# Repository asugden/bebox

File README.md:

#BEBOX

BeBox is a collection of tools for systems neuroscience. It includes three parts: designs for 3d printing, circuits and printed circuit boards (PCBs) for behavioral manipulation, and the Arduino code necessary for those circuits.

Many people are interested in only the 3d designs. In that case, all necessary hardware components are listed in the 3d designs directory. If you are interested in electronics, the BeBox Spritz and the BeBox Syringe Pump can both be used indepent of the BeBox system. The syringe pump can be integrated with BeBox. To start with BeBox, one has to order the boards (links can be found in the pcb directory), which come in orders of 3 from OSH Park, my preferred supplier. Note that BeBox is connected by 4-conductor headphone cables. They can be a bit hard to find. 3-conductor cables will not work.

##3D DESIGNS:
__All necessary components are listed in the README in the 3d directory.__

- .stl files  are final output files to be used with 3D printers.
- .scad files  are files written in OpenSCAD which define the .stl files and can be edited
- Some designs are made in Fusion 360 and are available upon request.

###bebox
- bebox bnc bottom.stl  the bottom of a case to hold bnc connectors for bebox
- bebox bnc top.stl  the top of the case to hold bnc connectors for bebox, which can have magnets inserted to allow stacking
- bebox button bottom.stl  the bottom of a case to hold bebox buttons, which also reports licks
- bebox button top.stl  the top of the case to hold bebox buttons
- bebox button 1.stl  a button cap with the number 1
- bebox button 2.stl  a button cap with the number 2
- bebox button 3.stl  a button cap with the number 3
- bebox button 4.stl  a button cap with the number 4
- bebox button e.stl  a button cap with the number e, for ensure
- bebox button q.stl  a button cap with the letter q, for quinine
- bebox main bottom.stl  the bottom of the case to hold the main bebox board
- bebox main top.stl  the top of the case to hold the main bebox board

###lickspout
__NOTE:__ the lickspouts should be printed with conductive PLA if conductive measurement is desired. The lickspout base should be printed in regular PLA. Conductive PLA plastic can be found at https://www.proto-pasta.com/collections/exotic-composite-pla/products/conductive-pla

- lickspout bitube.stl  a pre-made file to be printed with conductive filament that has two tubes, one regularly used for ensure high-calorie milkshake and one used for quinine diluted in water. This is designed for Tygon tubing of 1/16 inch inner diameter and 1/8 inch outer diameter (1.6 mm ID/3.2 mm OD). 
- lickspout unitube.stl  a pre-made file to be printed with conductive filament that has a single tube with a collection area, for training on only a high-calorie milkshake
- lickspout.scad  the file used to create both lickspout bitube and lickspout unitube. Adjustments can be made to the tube diameters at the top. Note that the curved pipe library is required for making changes: https://www.thingiverse.com/thing:71464
- lickspout bitube water.stl  a pre-made file to be printed with conductive filament that has two narrow-diameter tubes. The input tubing should be the same diameter, but the flow rate is decreased
- lickspout water.scad  the file used to create lickspout bitube water.stl. This, too, depends on the curved pipe library
- utilities.scad  a set of useful functions for OpenSCAD

###syringe-pump
The syringe pump is designed to tightly fit 20 ml syringes. All necessary mechanical and electrical components are listed in the README of the syringe 

- syringe pump box.stl  a file that defines the enclosure of the syringe pump including the motor and carriage
- syringe pump carriage.stl  the carriage that rides along bearings to compress the syringe. Note that it should be printed vertically rather than on a flat face.

###wheel
- wheel.stl  a pre-made file that can be printed on an average FDM printer with minimal layer heights. This requires two M4 nuts to be embedded and two M4x10 bolts to pinch the axles. I recommend using black PLA for the wheel as other colors may not correctly block the IR light of a beam breaker. We had problems with gray PLA being transparent to IR light.
- wheel axle.stl  a pre-made file of a short axle piece used to attach the wheel to the wheel holder. 2 are required
- wheel holder.stl  a pre-made file of a suspension system for the wheel, designed to fit into standard Thorlabs pieces. Requires two bearings from McMaster-Carr catalog number 57155K323 at $5.70 each to be inserted into the large central holes with the flanges outward. We hot glue them in, taking care not to get the glue into the bearings.
- wheel.scad  the file used to create wheel.stl. The wheel height, diameter, and tab spacing can all be changed. Note that a finer tab spacing requires narrower LED beam break detectors-- do not change without changing the encoder board.
- wheel holder.scad  the file used to create wheel axle.stl. The spring width, length, and thickness can all be adjusted and the wheel position will remain constant.

###wheel-accessories
- wheel run stopper.stl  a pre-made file that fits into a thorlabs part and applies some resistance to the wheel without disrupting its low inertia/springiness
- wheel run stopper.scad  the file used to create wheel run stopper.stl

###wheel-encoder
__NOTE:__ will be udpated in the near future

- wheel arduino holder.stl  a file to hold two LED beam breakers adjacent to the wheel
- wheel encoder board holder.stl  a file to allow an arduino to be bolted on to the holder such that it can be held next to the wheel

##ARDUINO CODE:
__NOTE:__ Has not yet been made compatible with the new BeBox system. Will be updated soon.

- BeBox  the code to run the BeBox system
	- mpr121.h  the header definitions required for the capacitance lick detection system

- Dumberbox  the code used to run the legacy Dumbberbox
- Encoder_Scanbox  the code used to run the legacy scanbox rotary encoder. Will be replaced with BeBox encoder software in early April 2019.

##PCB DESIGNS:
__All necessary components are listed in the README in the pcb directory.__

- .brd files  board files, matched with their schematic file, made in Eagle. You can bypass dealing with these files by directly ordering from OSH Park through a link I've set up. I am not affiliated with OSH Park.
- .sch files  schematic files, matched with a board file, made in Eagle. 

__NOTE:__  PCBs can be ordered from OSH Park for low costs. As of now, they are untested so please wait until late March 2019

- bebox_main  the main board, which takes power and connects directly to high-current behavior systems such as solenoids. It passed on the power given to it (usually 12V 2A supply, but can be 6-13 V and > 1 A). It connects via headphone cables to the daughter boards and lick spout. The connection ports are interchangeable.
- bebox_bnc  a daughterboard that allows for connections with Matlab via a Nidaq BNC system. It includes the lick detection and 4 output solenoids
- bebox_buttons  a daughterboard that allows control of solenoids and reports licking. There are two lick detection LEDs, just in case, and four buttons to control solenoids.
- bebox_encoder  a board that holds the rotary encoder IR beam breakers adjacent to the running wheel. This board can be configured in one of three ways: 
	1. For connection to the BeBox system, one can solder on an Adafruit Metro Mini (an Arduino Uno clone that has been miniaturized) and the i2c headphone jack. This will allow BeBox to directly interact with the running encoder. 
	2. To connect to Neurolabware's Scanbox, one can solder on an Adafruit Metro Mini and no headphone jacks. This can be plugged directly into the Scanbox computer via USB and it will be indistinguishable from an Arduino Uno.
	3. To use this with systems sensitive to electrical noise (electrophysiology), one can solder on the "ephys only" headphone jack, which transmits ground, power, and the output of the two beam breakers. This i2c cable can pass outside of a faraday cage to an external Arduino.

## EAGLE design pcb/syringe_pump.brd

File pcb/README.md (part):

__NOTE: I get no money from this and have no affiliation with OSH Park.__

## BeBox Main Trinket components

__CONFIRMED TO WORK__: https://oshpark.com/shared_projects/5AUOipvb

After creating this PCB, the Trinket became deprecated. I have created a newer, faster version based on the Adafruit ItsyBitsy M4.

| Part name            | Count | Cost per part | Total cost | Vendor  | Vendor part number | 
|----------------------|-------|---------------|------------|---------|--------------------| 
| headone jack         | 4     | 1.66          | 6.64       | Digikey | CP-435107RS-ND     | 
| 4.7k resistor        | 6     | 0.10          | 0.60       | Digikey | CF14JT4K70CT-ND    | 
| power jack           | 1     | 0.76          | 0.76       | Digikey | CP-102AH-ND        | 
| screw terminal       | 4     | 0.75          | 3.00       | Digikey | ED2740-ND          | 
| switch               | 1     | 11.56         | 11.56      | Digikey | 679-3961-ND        | 
| diode                | 4     | 0.11          | 0.44       | Digikey | 641-1310-1-ND      | 
| transistor           | 4     | 0.70          | 2.80       | Digikey | TIP122GOS-ND       | 
| adafruit pro trinket | 1     | 9.95          | 9.95       | Digikey | 1528-1039-ND       | 

## BeBox Main ItsyBitsy components

https://oshpark.com/shared_projects/iDtDUlNY

This new version is based on the Adafruit ItsyBitsy M4, but requires conversion for logic levels.

| Part name              | Count | Cost per part | Total cost | Vendor  | Vendor part number | 
|------------------------|-------|---------------|------------|---------|--------------------| 
| headone jack           | 4     | 1.66          | 6.64       | Digikey | CP-435107RS-ND     | 
| 4.7k resistor          | 8     | 0.10          | 0.60       | Digikey | CF14JT4K70CT-ND    | 
| power jack             | 1     | 0.76          | 0.76       | Digikey | CP-102AH-ND        | 
| screw terminal         | 4     | 0.75          | 3.00       | Digikey | ED2740-ND          | 
| switch                 | 1     | 11.56         | 11.56      | Digikey | 679-3961-ND        | 
| diode                  | 4     | 0.11          | 0.44       | Digikey | 641-1310-1-ND      | 
| transistor             | 4     | 0.70          | 2.80       | Digikey | TIP122GOS-ND       | 
| adafruit itsybitsy m4  | 1     | 9.95          | 9.95       | Digikey | 1528-1039-ND       | 
| logic level transistor | 2     | 0.47          | 0.94       | Digikey | 2N7000FS-ND        | 
| 5V regulator           | 1     | 6.81          | 20.43      | Digikey | 945-1037-ND        | 

## BeBox BNC components

__CONFIRMED TO WORK__: https://oshpark.com/shared_projects/NPiqw07m

This box breaks out BNCs for communication with NIDAQ boards or the like. Currently, there is only a single lick output. Although the rest of BeBox can handle two capacitive sensors, the BNC board is not yet adapted for 4 solenoids and 2 licks. It is easy to change the code such that one of the solenoid inputs can be converted to a second lick output.

| Part name       | Count | Cost per part | Total cost | Vendor  | Vendor part number | 
|-----------------|-------|---------------|------------|---------|--------------------| 
| bnc onnector    | 5     | 1.65          | 8.25       | Digikey | A97555-ND          | 
| headphone jack  | 1     | 1.66          | 1.66       | Digikey | CP-435107RS-ND     | 
| i2c io expander | 1     | 1.05          | 1.05       | Digikey | MCP23008-E/P-ND    | 
| 4.7k resistor   | 5     | 0.10          | 0.50       | Digikey | CF14JT4K70CT-ND    | 

## BeBox Button components

__CONFIRMED TO WORK__: https://oshpark.com/shared_projects/y1Swevmm

This box has buttons to control solenoids, as well as two LEDs that represent responses to different capacitance inputs. Our printer and slicer do a poor job keeping the inside of the LED holes clean, so it sometimes needs to be cleaned out with a 5 mm / 3/16 inch drill bit.

| Part name       | Count | Cost per part | Total cost | Vendor  | Vendor part number | 
|-----------------|-------|---------------|------------|---------|--------------------| 
| headphone jack  | 1     | 1.66          | 1.66       | Digikey | CP-435107RS-ND     | 
| i2c io expander | 1     | 1.05          | 1.05       | Digikey | MCP23008-E/P-ND    | 
| switch (cherry) | 4     | 0.90          | 3.60       | Digikey | CH310-ND           | 
| 330 resistor    | 2     | 0.10          | 0.20       | Digikey | CF14JT330RCT-ND    | 
| red led         | 1     | 0.33          | 0.33       | Digikey | 160-1853-ND        | 
| yellow led      | 1     | 0.33          | 0.33       | Digikey | 160-1851-ND        | 

## BeBox cables

You need 4-conductor 3.5 mm headphone cables to connect BeBox components. They can be any length. Two cables are required for the main 3 boxes, but more need to be used for the encoder or syringe pump. Below are options– you can choose how many to order of each size.

| Part name  | Count | Cost per part | Total cost | Vendor    | Vendor part number | 
|------------|-------|---------------|------------|-----------|--------------------| 
| 1' cable   | 1     | 1.50          | 1.50       | Digikey   | CAB-14163-ND       | 
| 3' cable   | 1     | 2.50          | 2.50       | Digikey   | CAB-14164-ND       | 
| 6' cable   | 1     | 6.45          | 6.45       | Digikey   | CP-354S-M/M-ND     | 
| 1' cable   | 1     | 1.89          | 1.89       | Monoprice | 24437              | 
| 3' cable   | 1     | 2.29          | 2.29       | Monoprice | 18632              | 
| 6' cable   | 1     | 2.59          | 2.59       | Monoprice | 18633              | 

## BeBox Capacitance Lickspout components

__CONFIRMED TO WORK__

There is no PCB here. We simply order a capacitance-sensing board and wire in the 4-conductor headphone cable. One prints a capacitance lickspout, uses an M3 bolt to fasten it to the lickspout holder, solder headers into the capacitance sensing board, heat a wire and shove it into the lickspout, and then attach it to the capacitance sensing board (again with headers, so that the lickspout can be replaced often).

__CONNECT BLACK -> SCL, YELLOW -> SDA, GREEN -> GND, RED -> VIN__

Note that wires are connected differently from dumberboxes.

| Part name          | Count | Cost per part | Total cost | Vendor  | Vendor part number | 
|--------------------|-------|---------------|------------|---------|--------------------| 
| capacitance sensor | 1     | 7.95          | 7.95       | Digikey | CP-435107RS-ND     | 
| 4-conductor wire   | 1     | 6.25          | 6.25       | Digikey | CP-354S-ND         | 
| female header      | 1     | 0.32          | 0.32       | Digikey | S7000-ND           | 

## BeBox Encoder components

https://oshpark.com/shared_projects/I9CImQTS

| Part name           | Count | Cost per part | Total cost | Vendor  | Vendor part number | 
|---------------------|-------|---------------|------------|---------|--------------------| 
| ir beam break       | 2     | 3.77          | 7.54       | Digikey | 1855-1043-ND       | 
| 220 resistor        | 2     | 0.10          | 0.20       | Digikey | CF14JT220RCT-ND    | 
|                     |       |               |            |         |                    | 
| OPTIONAL:           |       |               |            |         |                    | 
| adafruit metro mini | 1     | 12.50         | 12.50      | Digikey | 1528-1374-ND       | 
| headphone jack      | 1     | 1.66          | 1.66       | Digikey | CP-435107RS-ND     | 

This board can be configured in one of three ways: 

1. For connection to the BeBox system, one can solder on an Adafruit Metro Mini (an Arduino Uno clone that has been miniaturized) and the i2c headphone jack. This will allow BeBox to directly interact with the running encoder.  __(both optional components)__
2. To connect to Neurolabware's Scanbox, one can solder on an Adafruit Metro Mini and no headphone jacks. This can be plugged directly into the Scanbox computer via USB and it will be indistinguishable from an Arduino Uno.  __(only optional metro mini)__
3. To use this with systems sensitive to electrical noise (electrophysiology), one can solder on the "ephys only" headphone jack, which transmits ground, power, and the output of the two beam breakers. This i2c cable can pass outside of a faraday cage to an external Arduino.  __(only optional headphone jack)__

## BeBox Syringe Pump components

https://oshpark.com/shared_projects/pRGppHBK

The syringe pump also requires a replaceable 20 ml syringe.

| Part name                                 | Count | Cost per part | Total cost | Vendor  | Vendor part number    | 
|-------------------------------------------|-------|---------------|------------|---------|-----------------------| 
| adafruit itsybitsy m4                     | 1     | 14.95         | 14.95      | Digikey | 1528-2619-ND          | 
| stepper driver                            | 1     | 7.98          | 23.94      | Digikey | 1460-1159-ND          | 
| 5V regulator                              | 1     | 6.81          | 20.43      | Digikey | 945-1037-ND           | 
| oled screen                               | 1     | 19.95         | 19.95      | Digikey | 1528-1512-ND          | 
| switch (cherry MX clear)                  | 1     | 0.90          | 0.90       | Digikey | CH310-ND              | 
| rotary encoder (long)                     | 1     | 1.73          | 1.73       | Digikey | PEC11R-4020F-S0012-ND | 
| forward-backward toggle switch            | 1     | 4.32          | 4.32       | Digikey | 360-3355-ND           | 
| on-off toggle switch                      | 1     | 5.96          | 5.96       | Digikey | M2012S2A2A30-ND       | 
| power jack                                | 1     | 0.76          | 0.76       | Digikey | CP-102AH-ND           | 
| screw terminal                            | 4     | 0.75          | 3.00       | Digikey | ED2740-ND             | 
| heat sink pad                             | 1     | 3.44          | 3.44       | Digikey | 3M10304-ND            | 
| heatsink                                  | 1     | 0.49          | 1.47       | Digikey | AE11388-ND            | 
| logic level transistor                    | 2     | 0.47          | 0.94       | Digikey | 2N7000FS-ND           | 
| 4.7k resistor                             | 4     | 0.10          | 0.40       | Digikey | CF14JT4K70CT-ND       | 
| 3.5mm jack                                | 1     | 1.66          | 1.66       | Digikey | CP-435107RS-ND        | 
| stepper motor (NEMA 17 200 steps/rev 12V) | 1     | 14.00         | 14.00      | Digikey | 1528-1062-ND          | 

## BeBox Spritz components

https://oshpark.com/shared_projects/YoxiTIt1

This is a device to produce very small amounts of pressure for microinjections or puffing of drugs onto slices.

| Part name                | Count | Cost per part | Total cost | Vendor   | Vendor part number    | 
|--------------------------|-------|---------------|------------|----------|-----------------------| 
| adafruit itsybitsy m4    | 1     | 14.95         | 14.95      | Digikey  | 1528-2619-ND          | 
| 5V regulator             | 1     | 6.81          | 20.43      | Digikey  | 945-1037-ND           | 
| oled screen              | 1     | 19.95         | 19.95      | Digikey  | 1528-1512-ND          | 
| switch (cherry MX clear) | 2     | 0.90          | 1.80       | Digikey  | CH310-ND              | 
| rotary encoder (long)    | 1     | 1.73          | 1.73       | Digikey  | PEC11R-4020F-S0012-ND | 
| on-off toggle switch     | 1     | 5.96          | 5.96       | Digikey  | M2012S2A2A30-ND       | 
| power jack               | 1     | 0.76          | 0.76       | Digikey  | CP-102AH-ND           | 
| 150 resistor             | 1     | 0.10          | 0.10       | Digikey  | CF14JT150RCT-ND       | 
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
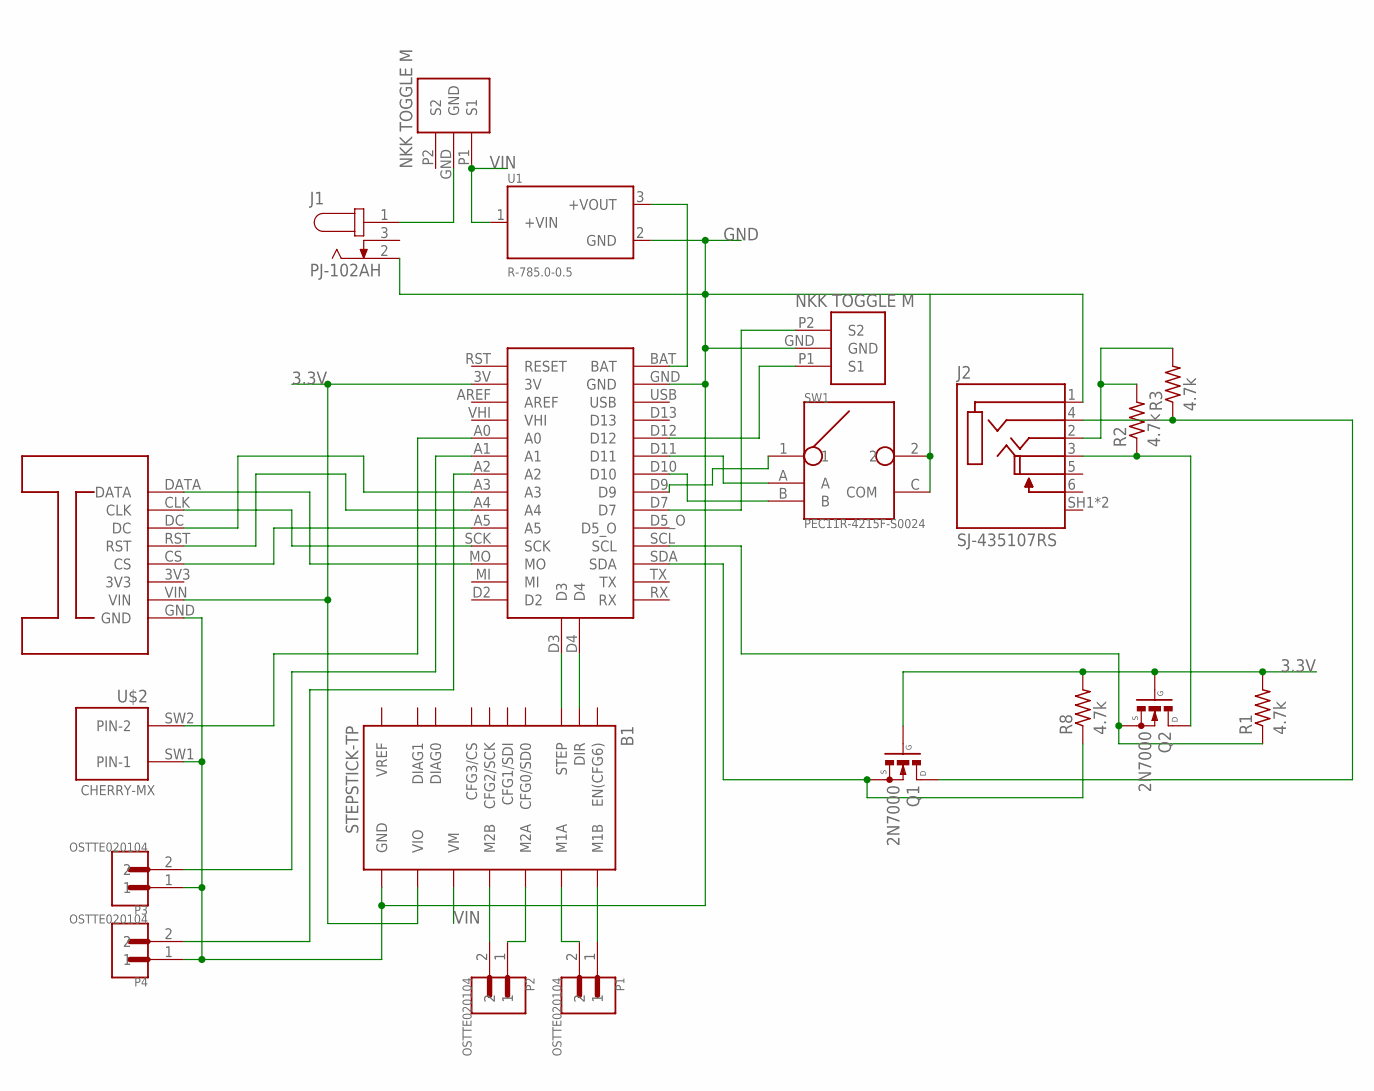
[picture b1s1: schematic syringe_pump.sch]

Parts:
B1: STEPSTICK-TP; STEPSTICK_TP
J1: PJ-102AH; CUI_PJ-102AH
J2: SJ-435107RS; CUI_SJ-435107RS
P1, P2, P3, P4: OSTTE020104; OST_OSTTE020104
Q1, Q2: 2N7000; TO92
R1, R2, R3, R8: 4.7k; 0207/10
SW1: PEC11R-4215F-S0024; SW_PEC11R-4215F-S0024
U1: R-785.0-0.5; RECOM_R-785.0-0.5
U$1: ITSYBITSYM4
U$2: CHERRY-MX
U$3: OLED_128X64
U$4: NKK_M2012S2A2A30
U$5: NKK_B13AH

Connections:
3.3V: B1.VIO, Q1.2 (G), Q2.2 (G), R1.2, R8.2, U$1.3V, U$3.VIN
GND: B1.GND@1 (GND), B1.GND@2 (GND), J1.2, J2.1 (SLEEVE), P3.1, P4.1, SW1.2, SW1.C (COM), U1.2 (GND), U$1.GND, U$2.SW1 (PIN-1), U$3.GND, U$5.GND
unnamed: Q1.1 (S), R8.1, U$1.SDA
unnamed: J2.2 (TIP), R2.2, R3.2
unnamed: B1.STEP, U$1.D3
unnamed: B1.DIR, U$1.D4
unnamed: Q2.1 (S), R1.1, U$1.SCL
unnamed: B1.M2B, P2.2
unnamed: B1.M2A, P2.1
unnamed: B1.M1B, P1.1
unnamed: B1.M1A, P1.2
unnamed: J2.3 (RING1), Q2.3 (D), R2.1
unnamed: J2.4 (RING2), Q1.3 (D), R3.1
unnamed: U$1.MO, U$3.DATA
unnamed: U$1.A3, U$3.DC
unnamed: U$1.A5, U$3.CS
unnamed: U$1.A4, U$3.RST
unnamed: P4.2, U$1.A2
unnamed: U$1.SCK, U$3.CLK
unnamed: J1.1, U$4.GND
unnamed: P3.2, U$1.A1
unnamed: U$1.A0, U$2.SW2 (PIN-2)
unnamed: U$1.D12, U$5.P1 (S1)
unnamed: U$1.D7, U$5.P2 (S2)
unnamed: SW1.A, U$1.D11
unnamed: SW1.B, U$1.D10
unnamed: SW1.1, U$1.D9
unnamed: U1.3 (+VOUT), U$1.BAT
VIN: B1.VM, U1.1 (+VIN), U$4.P1 (S1)

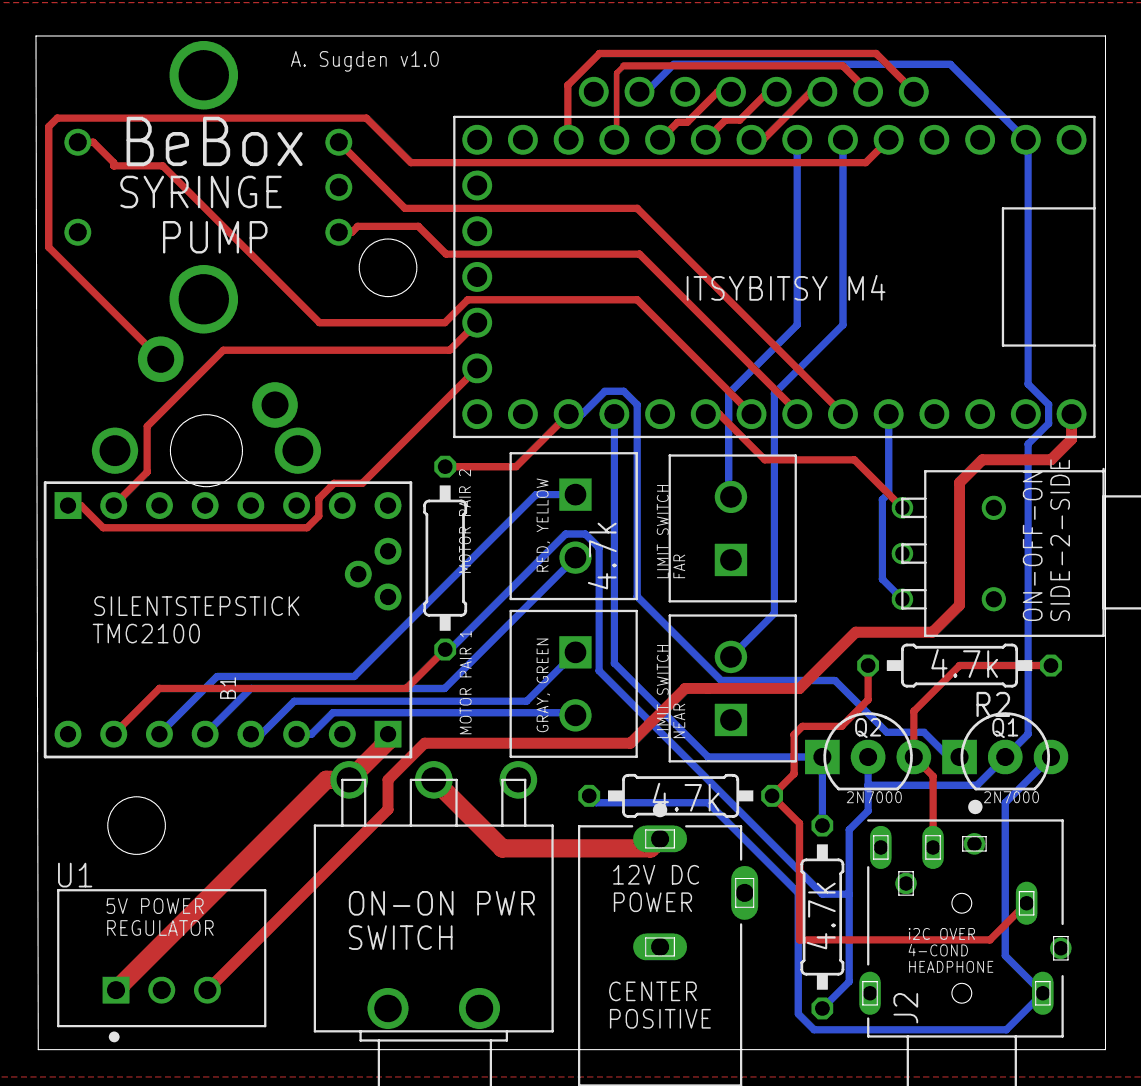
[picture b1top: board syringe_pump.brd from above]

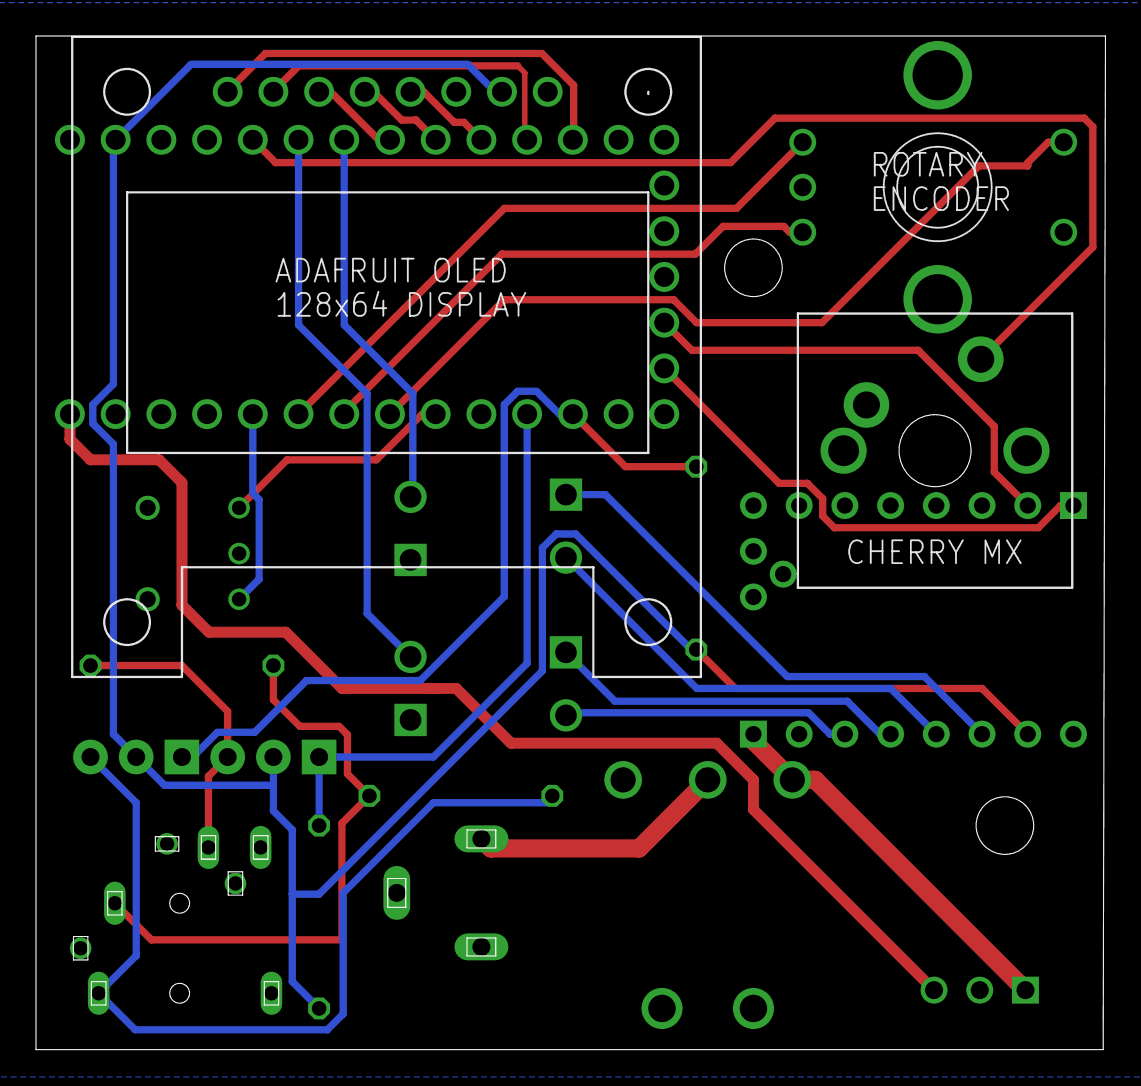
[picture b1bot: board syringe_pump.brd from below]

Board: 2 copper layers, 59.4 x 56.3 mm, 20 parts (3 on the bottom side), 29 nets.

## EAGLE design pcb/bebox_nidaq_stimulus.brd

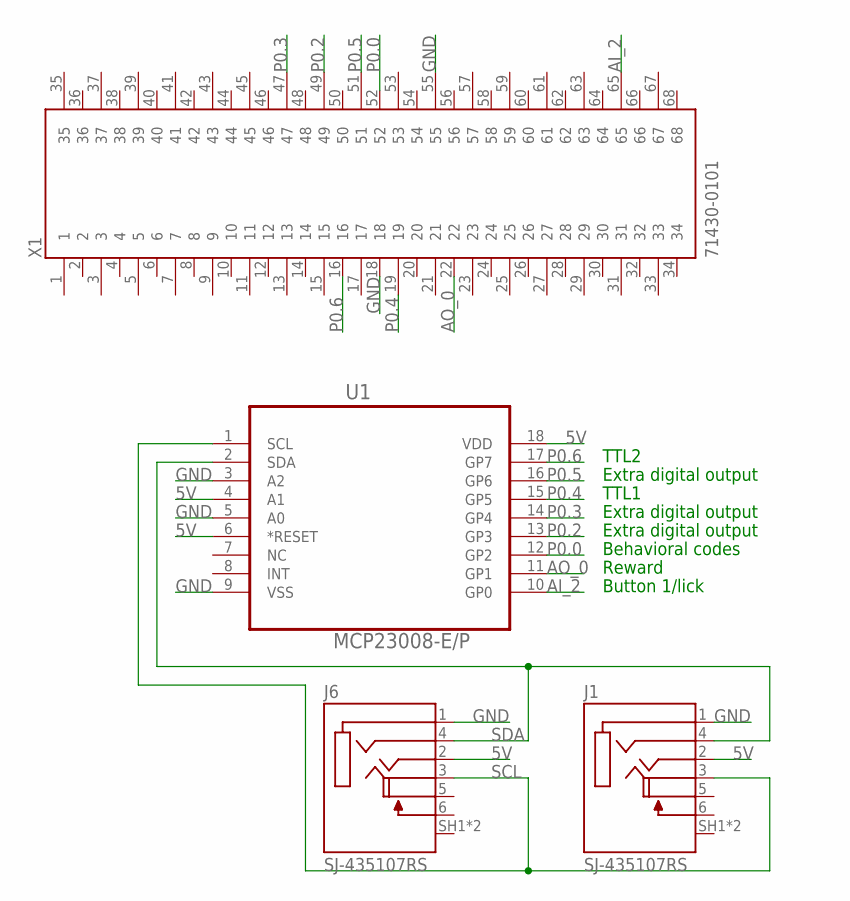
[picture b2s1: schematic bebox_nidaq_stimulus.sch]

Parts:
J1, J6: SJ-435107RS; CUI_SJ-435107RS
U1: MCP23008-E/P; DIP254P762X533-18
X1: 71430-0101; MOLEX_71430-0101

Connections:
5V: J1.2 (TIP), J6.2 (TIP), U1.4 (A1), U1.6 (*RESET), U1.18 (VDD)
AI_2: U1.10 (GP0), X1.65
AO_0: U1.11 (GP1), X1.22
GND: J1.1 (SLEEVE), J6.1 (SLEEVE), U1.3 (A2), U1.5 (A0), U1.9 (VSS), X1.18, X1.55
P0.0: U1.12 (GP2), X1.52
P0.2: U1.13 (GP3), X1.49
P0.3: U1.14 (GP4), X1.47
P0.4: U1.15 (GP5), X1.19
P0.5: U1.16 (GP6), X1.51
P0.6: U1.17 (GP7), X1.16
SCL: J1.3 (RING1), J6.3 (RING1), U1.1 (SCL)
SDA: J1.4 (RING2), J6.4 (RING2), U1.2 (SDA)

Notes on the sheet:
Reward
Behavioral codes
Button 1/lick
TTL1
TTL2
Extra digital output

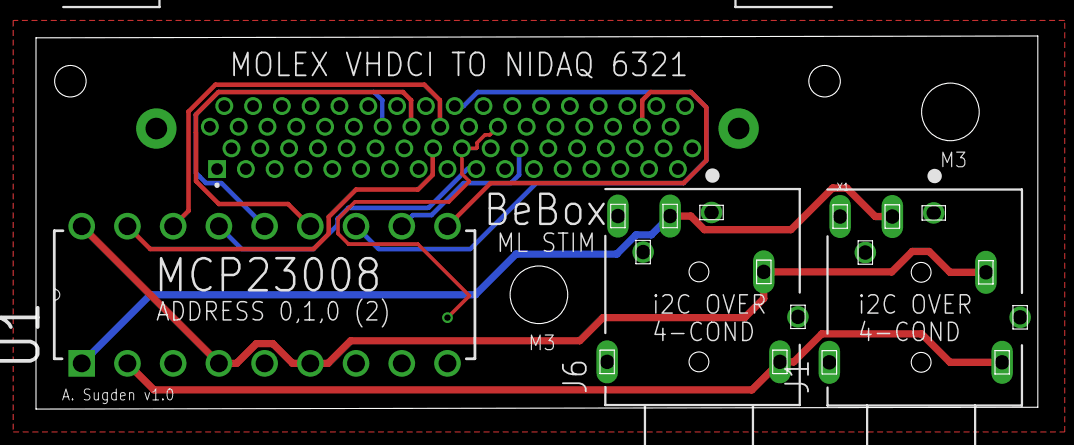
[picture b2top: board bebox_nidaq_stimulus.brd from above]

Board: 2 copper layers, 55.7 x 20.7 mm, 4 parts (0 on the bottom side), 12 nets.

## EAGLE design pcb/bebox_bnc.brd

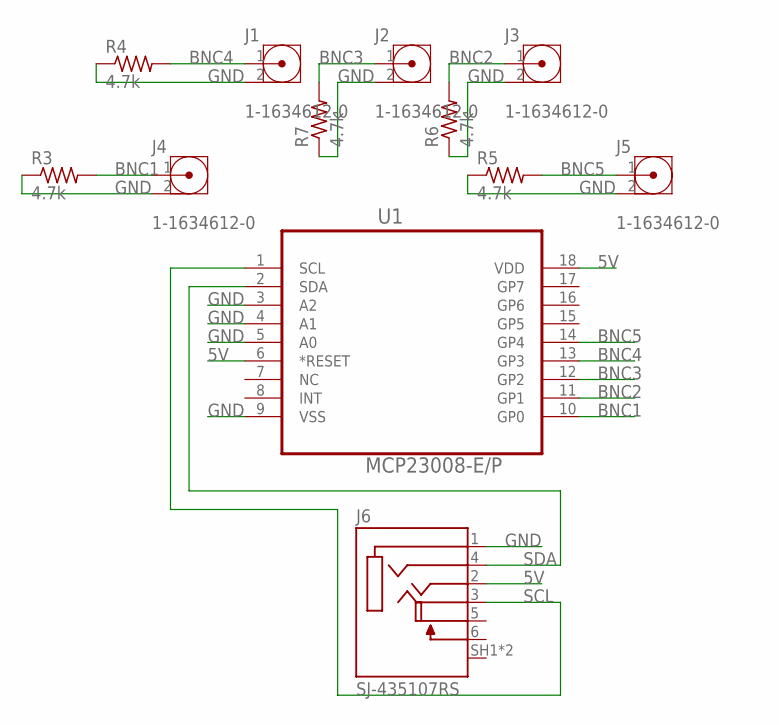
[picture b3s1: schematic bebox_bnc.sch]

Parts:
J1, J2, J3, J4, J5: 1-1634612-0; TE_1-1634612-0
J6: SJ-435107RS; CUI_SJ-435107RS
R3, R4, R5, R6, R7: 4.7k; 0207/10
U1: MCP23008-E/P; DIP254P762X533-18

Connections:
5V: J6.2 (TIP), U1.6 (*RESET), U1.18 (VDD)
BNC1: J4.1, R3.2, U1.10 (GP0)
BNC2: J3.1, R6.2, U1.11 (GP1)
BNC3: J2.1, R7.2, U1.12 (GP2)
BNC4: J1.1, R4.2, U1.13 (GP3)
BNC5: J5.1, R5.2, U1.14 (GP4)
GND: J1.2, J2.2, J3.2, J4.2, J5.2, J6.1 (SLEEVE), R3.1, R4.1, R5.1, R6.1, R7.1, U1.3 (A2), U1.4 (A1), U1.5 (A0), U1.9 (VSS)
SCL: J6.3 (RING1), U1.1 (SCL)
SDA: J6.4 (RING2), U1.2 (SDA)

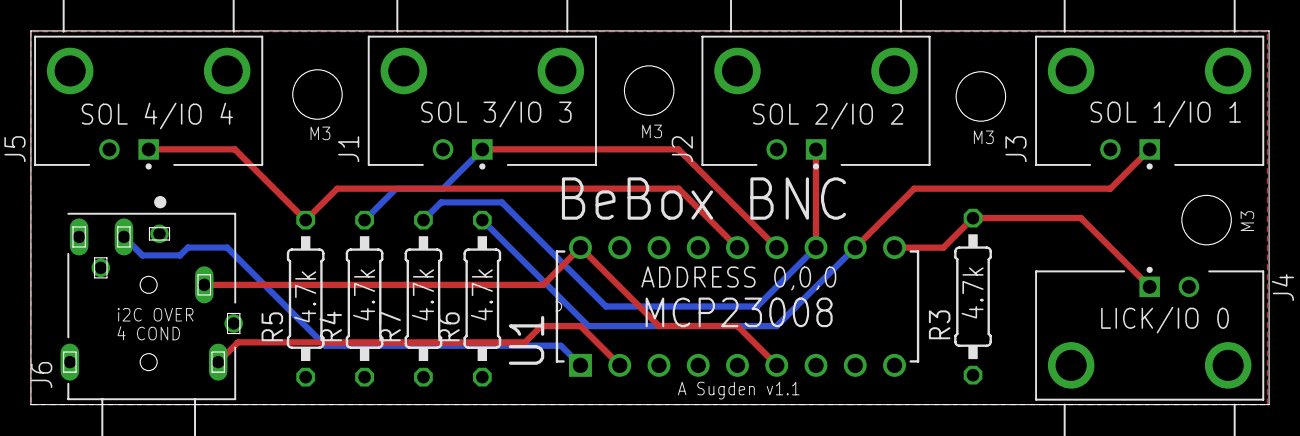
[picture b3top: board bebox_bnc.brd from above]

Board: 2 copper layers, 80.1 x 24.2 mm, 12 parts (0 on the bottom side), 9 nets.

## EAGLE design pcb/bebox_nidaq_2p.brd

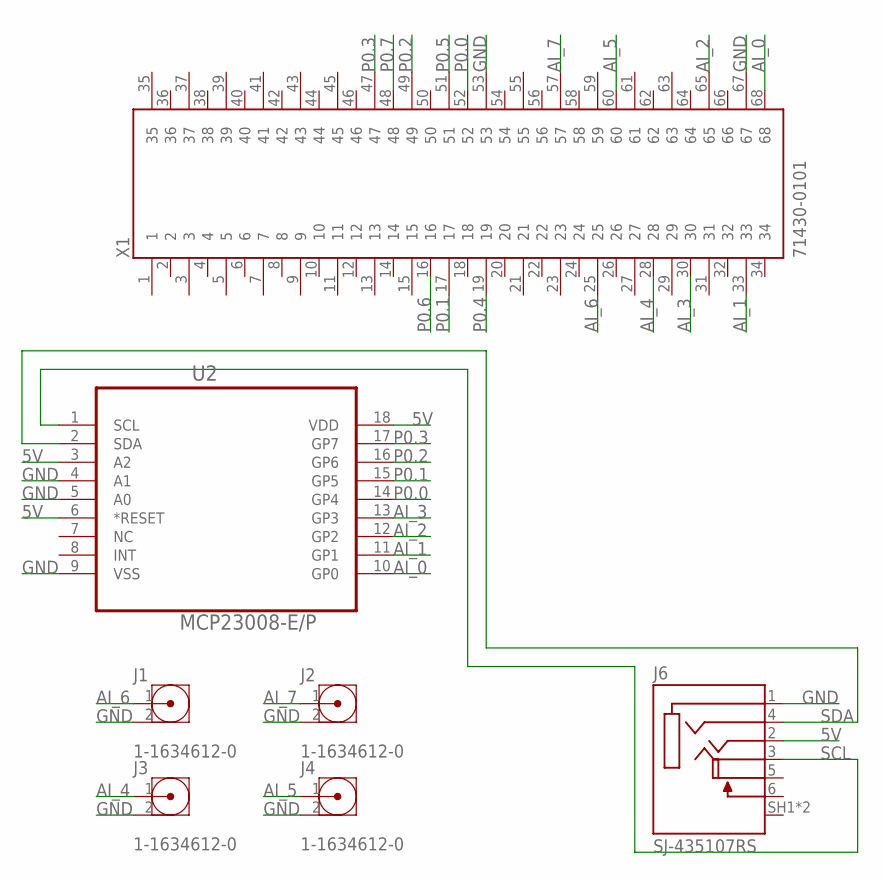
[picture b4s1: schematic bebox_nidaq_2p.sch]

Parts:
J1, J2, J3, J4: 1-1634612-0; TE_1-1634612-0
J6: SJ-435107RS; CUI_SJ-435107RS
U2: MCP23008-E/P; DIP254P762X533-18
X1: 71430-0101; MOLEX_71430-0101

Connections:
5V: J6.2 (TIP), U2.3 (A2), U2.6 (*RESET), U2.18 (VDD)
AI_0: U2.10 (GP0), X1.68
AI_1: U2.11 (GP1), X1.33
AI_2: U2.12 (GP2), X1.65
AI_3: U2.13 (GP3), X1.30
AI_4: J3.1, X1.28
AI_5: J4.1, X1.60
AI_6: J1.1, X1.25
AI_7: J2.1, X1.57
GND: J1.2, J2.2, J3.2, J4.2, J6.1 (SLEEVE), U2.4 (A1), U2.5 (A0), U2.9 (VSS), X1.53, X1.67
P0.0: U2.14 (GP4), X1.52
P0.1: U2.15 (GP5), X1.17
P0.2: U2.16 (GP6), X1.49
P0.3: U2.17 (GP7), X1.47
P0.4: X1.19
P0.5: X1.51
P0.6: X1.16
P0.7: X1.48
SCL: J6.3 (RING1), U2.1 (SCL)
SDA: J6.4 (RING2), U2.2 (SDA)

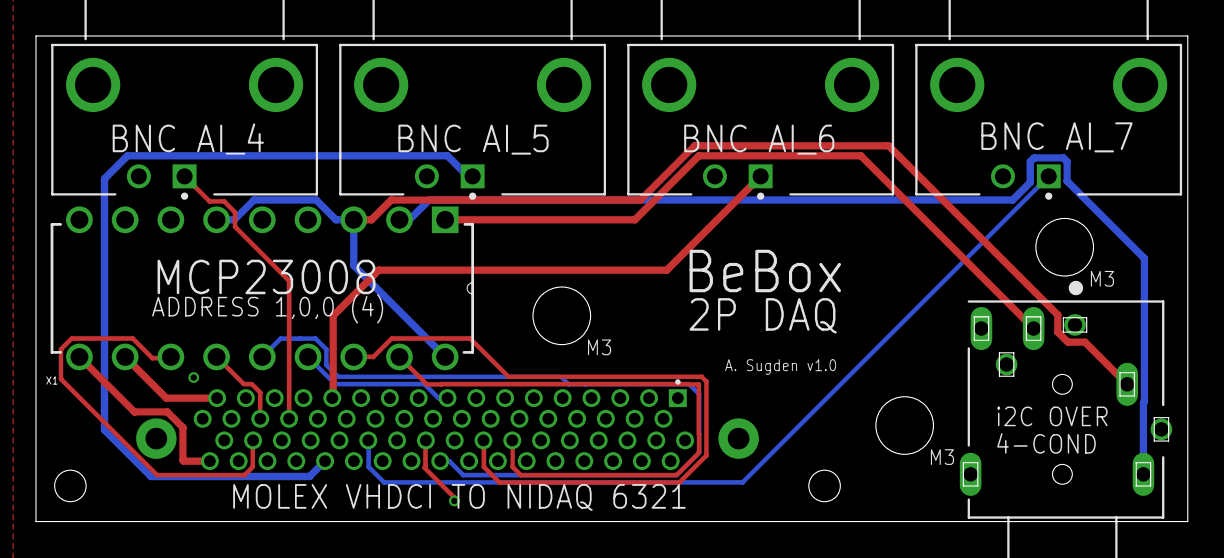
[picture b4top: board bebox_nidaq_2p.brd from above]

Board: 2 copper layers, 64.0 x 27.0 mm, 7 parts (0 on the bottom side), 16 nets.

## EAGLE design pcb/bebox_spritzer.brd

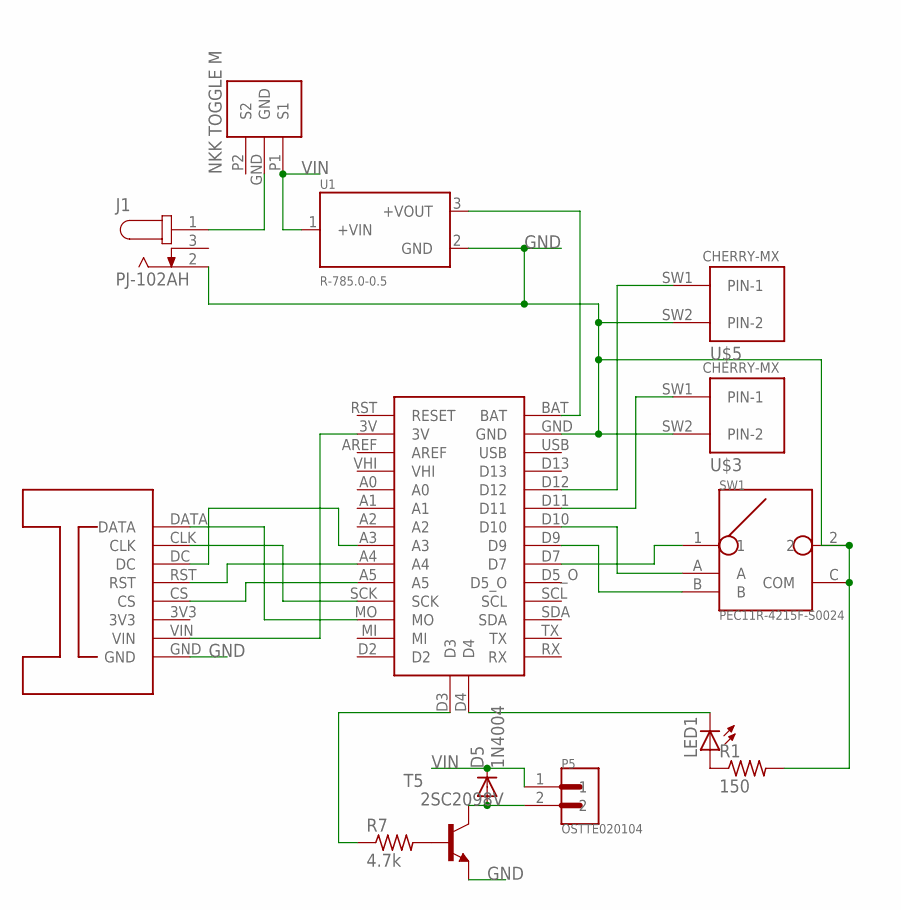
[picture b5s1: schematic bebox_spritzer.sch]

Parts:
D5: 1N4004; DO41-10
J1: PJ-102AH; CUI_PJ-102AH
LED1: LED5MM
P5: OSTTE020104; OST_OSTTE020104
R1: 150; 0207/10
R7: 4.7k; 0207/10
SW1: PEC11R-4215F-S0024; SW_PEC11R-4215F-S0024
T5: 2SC2098V; TO220AV
U1: R-785.0-0.5; RECOM_R-785.0-0.5
U$1: ITSYBITSYM4
U$2: OLED_128X64
U$3, U$5: CHERRY-MX
U$4: NKK_M2012S2A2A30

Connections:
GND: J1.2, R1.2, SW1.2, SW1.C (COM), T5.3 (E), U1.2 (GND), U$1.GND, U$2.GND, U$3.SW2 (PIN-2), U$5.SW2 (PIN-2)
unnamed: LED1.A, R1.1
unnamed: R7.1, U$1.D3
unnamed: LED1.K (C), U$1.D4
unnamed: U$1.D12, U$5.SW1 (PIN-1)
unnamed: U$1.MO, U$2.DATA
unnamed: U$1.SCK, U$2.CLK
unnamed: U$1.A3, U$2.DC
unnamed: U$1.A4, U$2.RST
unnamed: U$1.A5, U$2.CS
unnamed: R7.2, T5.1 (B)
unnamed: D5.A, P5.2, T5.2 (C)
unnamed: U$1.3V, U$2.VIN
unnamed: SW1.A, U$1.D10
unnamed: U$1.D11, U$3.SW1 (PIN-1)
unnamed: SW1.B, U$1.D9
unnamed: SW1.1, U$1.D7
unnamed: J1.1, U$4.GND
unnamed: U1.3 (+VOUT), U$1.BAT
VIN: D5.C, P5.1, U1.1 (+VIN), U$4.P1 (S1)

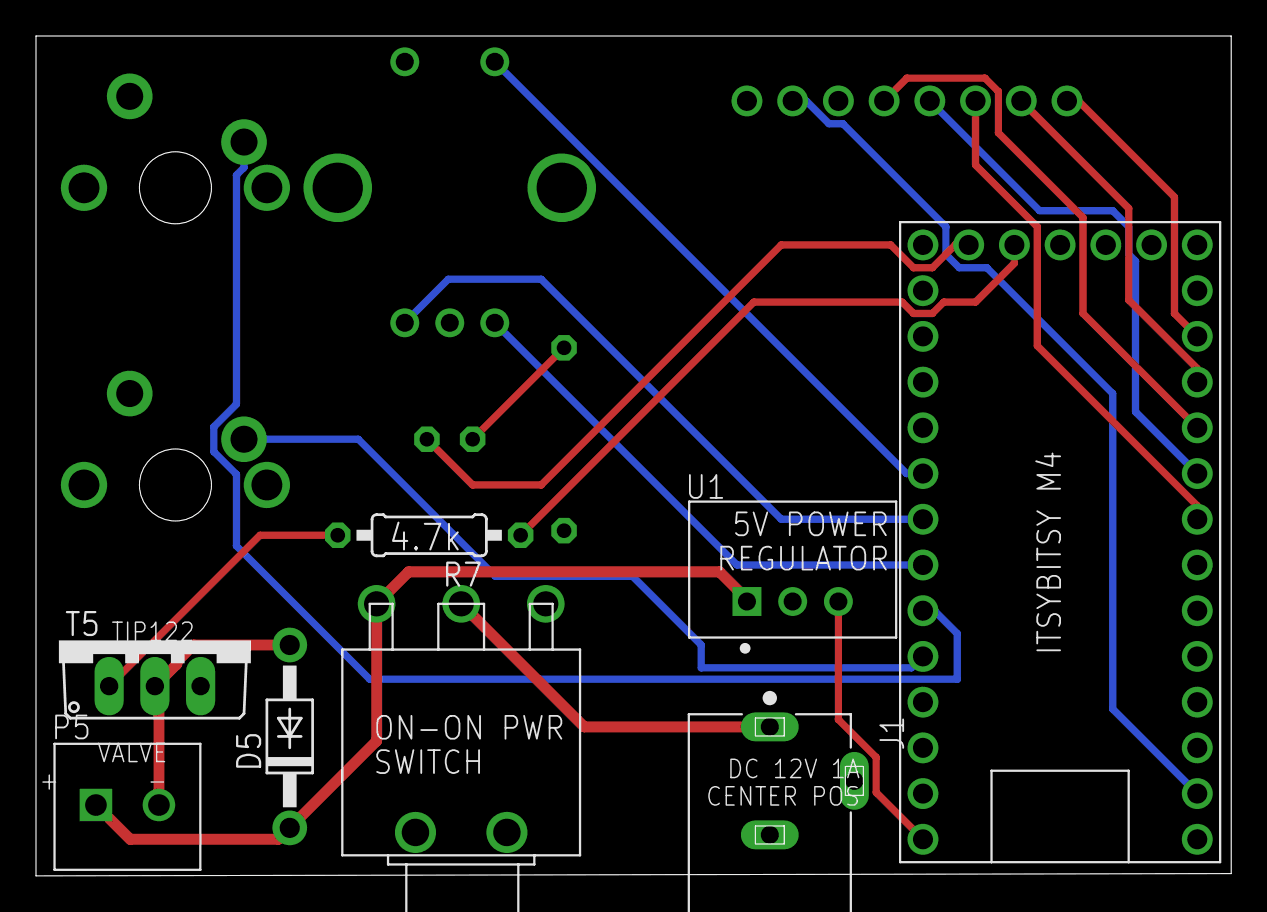
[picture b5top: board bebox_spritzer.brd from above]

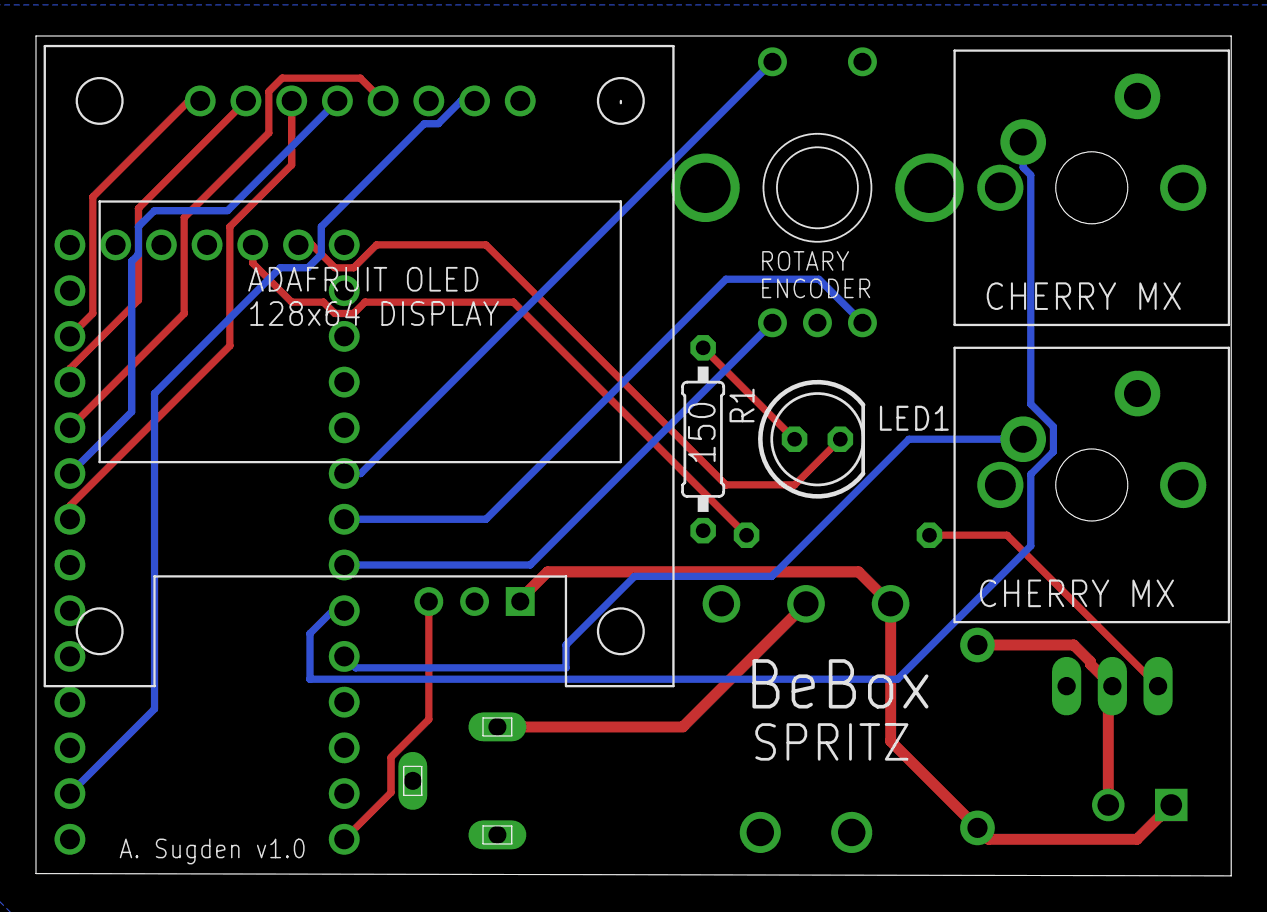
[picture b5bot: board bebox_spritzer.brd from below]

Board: 2 copper layers, 66.4 x 46.7 mm, 14 parts (6 on the bottom side), 20 nets.

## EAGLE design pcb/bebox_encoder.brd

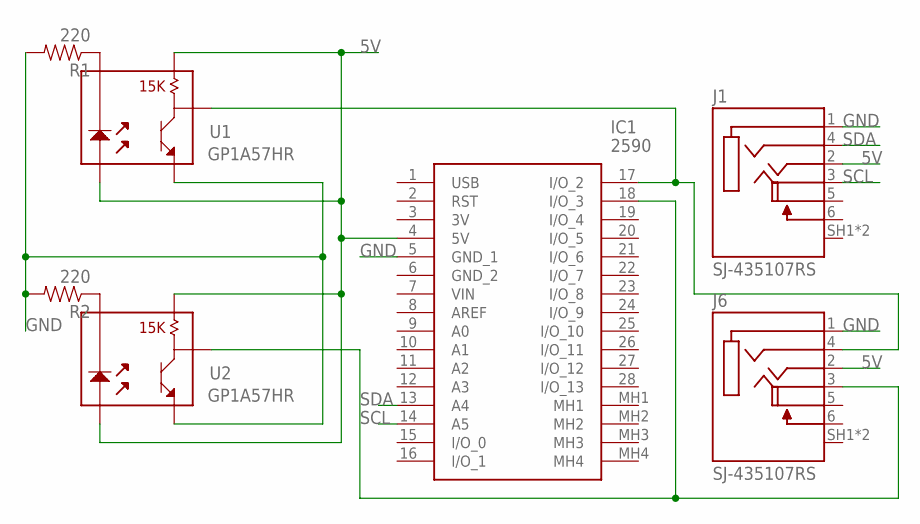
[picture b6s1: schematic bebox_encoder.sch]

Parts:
IC1: 2590
J1, J6: SJ-435107RS; CUI_SJ-435107RS
R1, R2: 220; AXIAL-0.3
U1, U2: GP1A57HR

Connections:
5V: IC1.4 (5V), J1.2 (TIP), J6.2 (TIP), U1.1, U1.3, U2.1, U2.3
GND: IC1.5 (GND_1), J1.1 (SLEEVE), J6.1 (SLEEVE), R1.P$2 (2), R2.P$2 (2), U1.5, U2.5
unnamed: R2.P$1 (1), U2.2
unnamed: R1.P$1 (1), U1.2
unnamed: IC1.17 (I/O_2), J6.4 (RING2), U1.4
unnamed: IC1.18 (I/O_3), J6.3 (RING1), U2.4
SCL: IC1.14 (A5), J1.3 (RING1)
SDA: IC1.13 (A4), J1.4 (RING2)

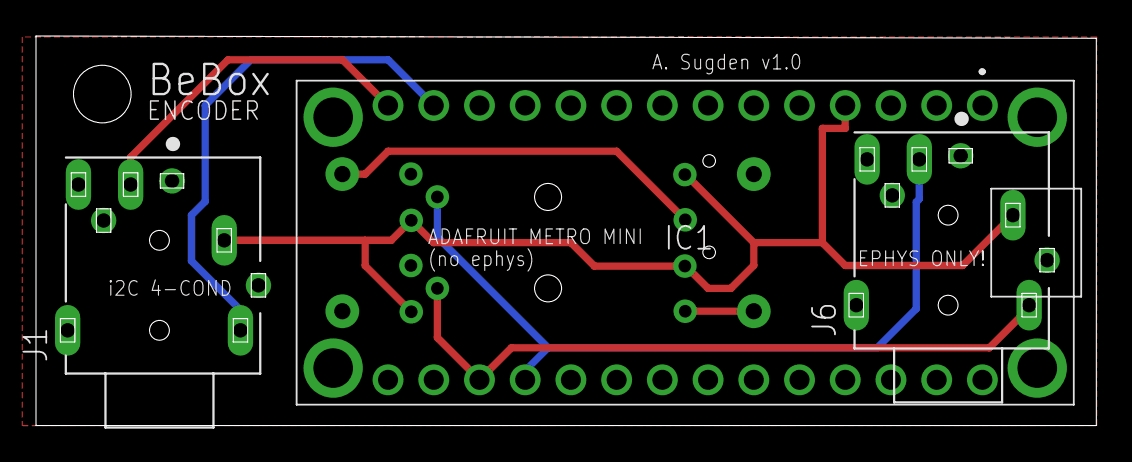
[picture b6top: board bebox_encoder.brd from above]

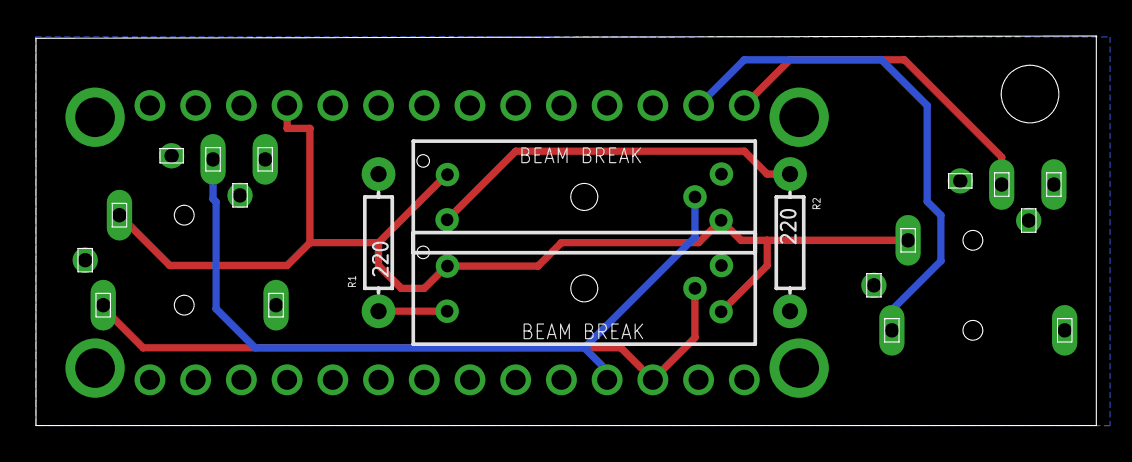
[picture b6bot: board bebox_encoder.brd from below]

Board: 2 copper layers, 58.9 x 21.6 mm, 7 parts (4 on the bottom side), 8 nets.

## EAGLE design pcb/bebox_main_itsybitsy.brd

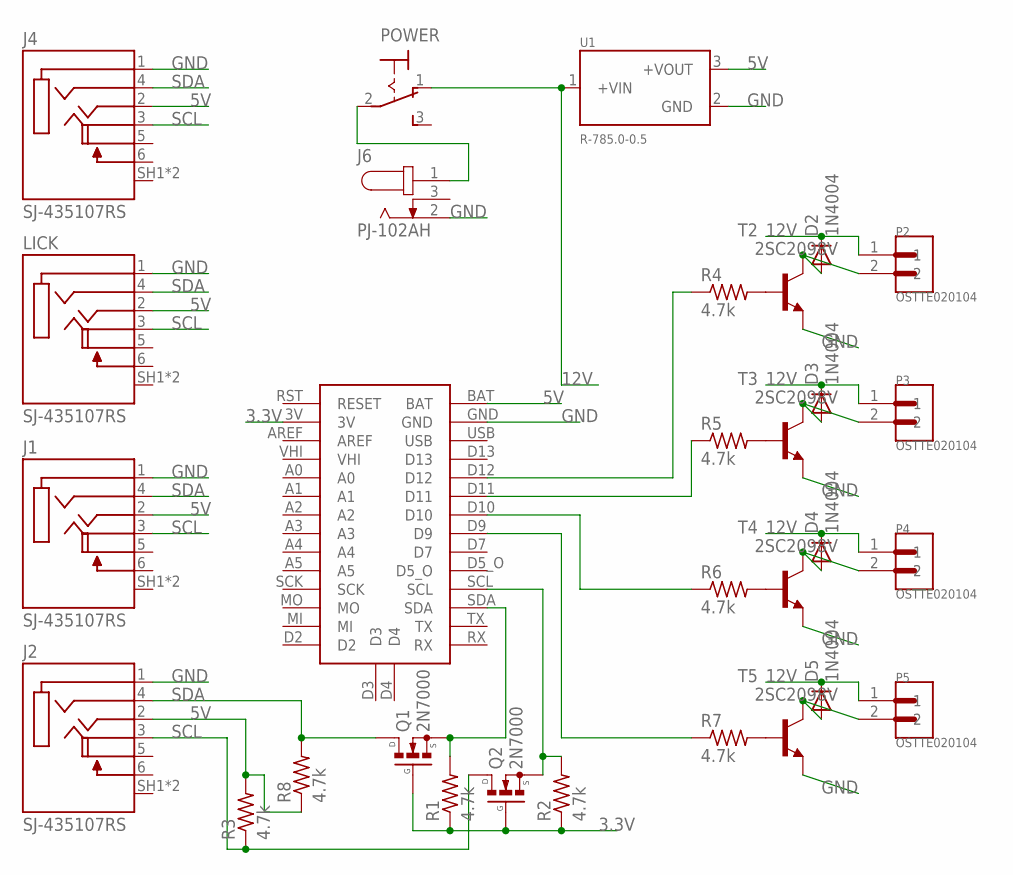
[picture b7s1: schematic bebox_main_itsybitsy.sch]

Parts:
D2, D3, D4, D5: 1N4004; DO41-10
J1, J2, J4: SJ-435107RS; CUI_SJ-435107RS
J6: PJ-102AH; CUI_PJ-102AH
LICK: SJ-435107RS; CUI_SJ-435107RS
P2, P3, P4, P5: OSTTE020104; OST_OSTTE020104
POWER: SWITCH_APEM_5636AB9; 320-916
Q1, Q2: 2N7000; TO92
R1, R2, R3, R4, R5, R6, R7, R8: 4.7k; 0207/10
T2, T3, T4, T5: 2SC2098V; TO220AV
U1: R-785.0-0.5; RECOM_R-785.0-0.5
U$1: ITSYBITSYM4

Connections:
3.3V: Q1.2 (G), Q2.2 (G), R1.1, R2.1, U$1.3V
5V: J1.2 (TIP), J2.2 (TIP), J4.2 (TIP), LICK.2 (TIP), R3.2, R8.1, U1.3 (+VOUT), U$1.BAT
12V: D2.C, D3.C, D4.C, D5.C, P2.1, P3.1, P4.1, P5.1, POWER.1 (O), U1.1 (+VIN)
GND: J1.1 (SLEEVE), J2.1 (SLEEVE), J4.1 (SLEEVE), J6.2, LICK.1 (SLEEVE), T2.3 (E), T3.3 (E), T4.3 (E), T5.3 (E), U1.2 (GND), U$1.GND
unnamed: J6.1, POWER.2
unnamed: Q1.1 (S), R1.2, U$1.SDA
unnamed: Q2.1 (S), R2.2, U$1.SCL
unnamed: R4.2, T2.1 (B)
unnamed: D2.A, P2.2, T2.2 (C)
unnamed: R5.2, T3.1 (B)
unnamed: D3.A, P3.2, T3.2 (C)
unnamed: R6.2, T4.1 (B)
unnamed: D4.A, P4.2, T4.2 (C)
unnamed: R7.2, T5.1 (B)
unnamed: D5.A, P5.2, T5.2 (C)
unnamed: R7.1, U$1.D9
unnamed: R6.1, U$1.D10
unnamed: R5.1, U$1.D11
unnamed: R4.1, U$1.D12
SCL: J1.3 (RING1), J2.3 (RING1), J4.3 (RING1), LICK.3 (RING1), Q2.3 (D), R3.1
SDA: J1.4 (RING2), J2.4 (RING2), J4.4 (RING2), LICK.4 (RING2), Q1.3 (D), R8.2
